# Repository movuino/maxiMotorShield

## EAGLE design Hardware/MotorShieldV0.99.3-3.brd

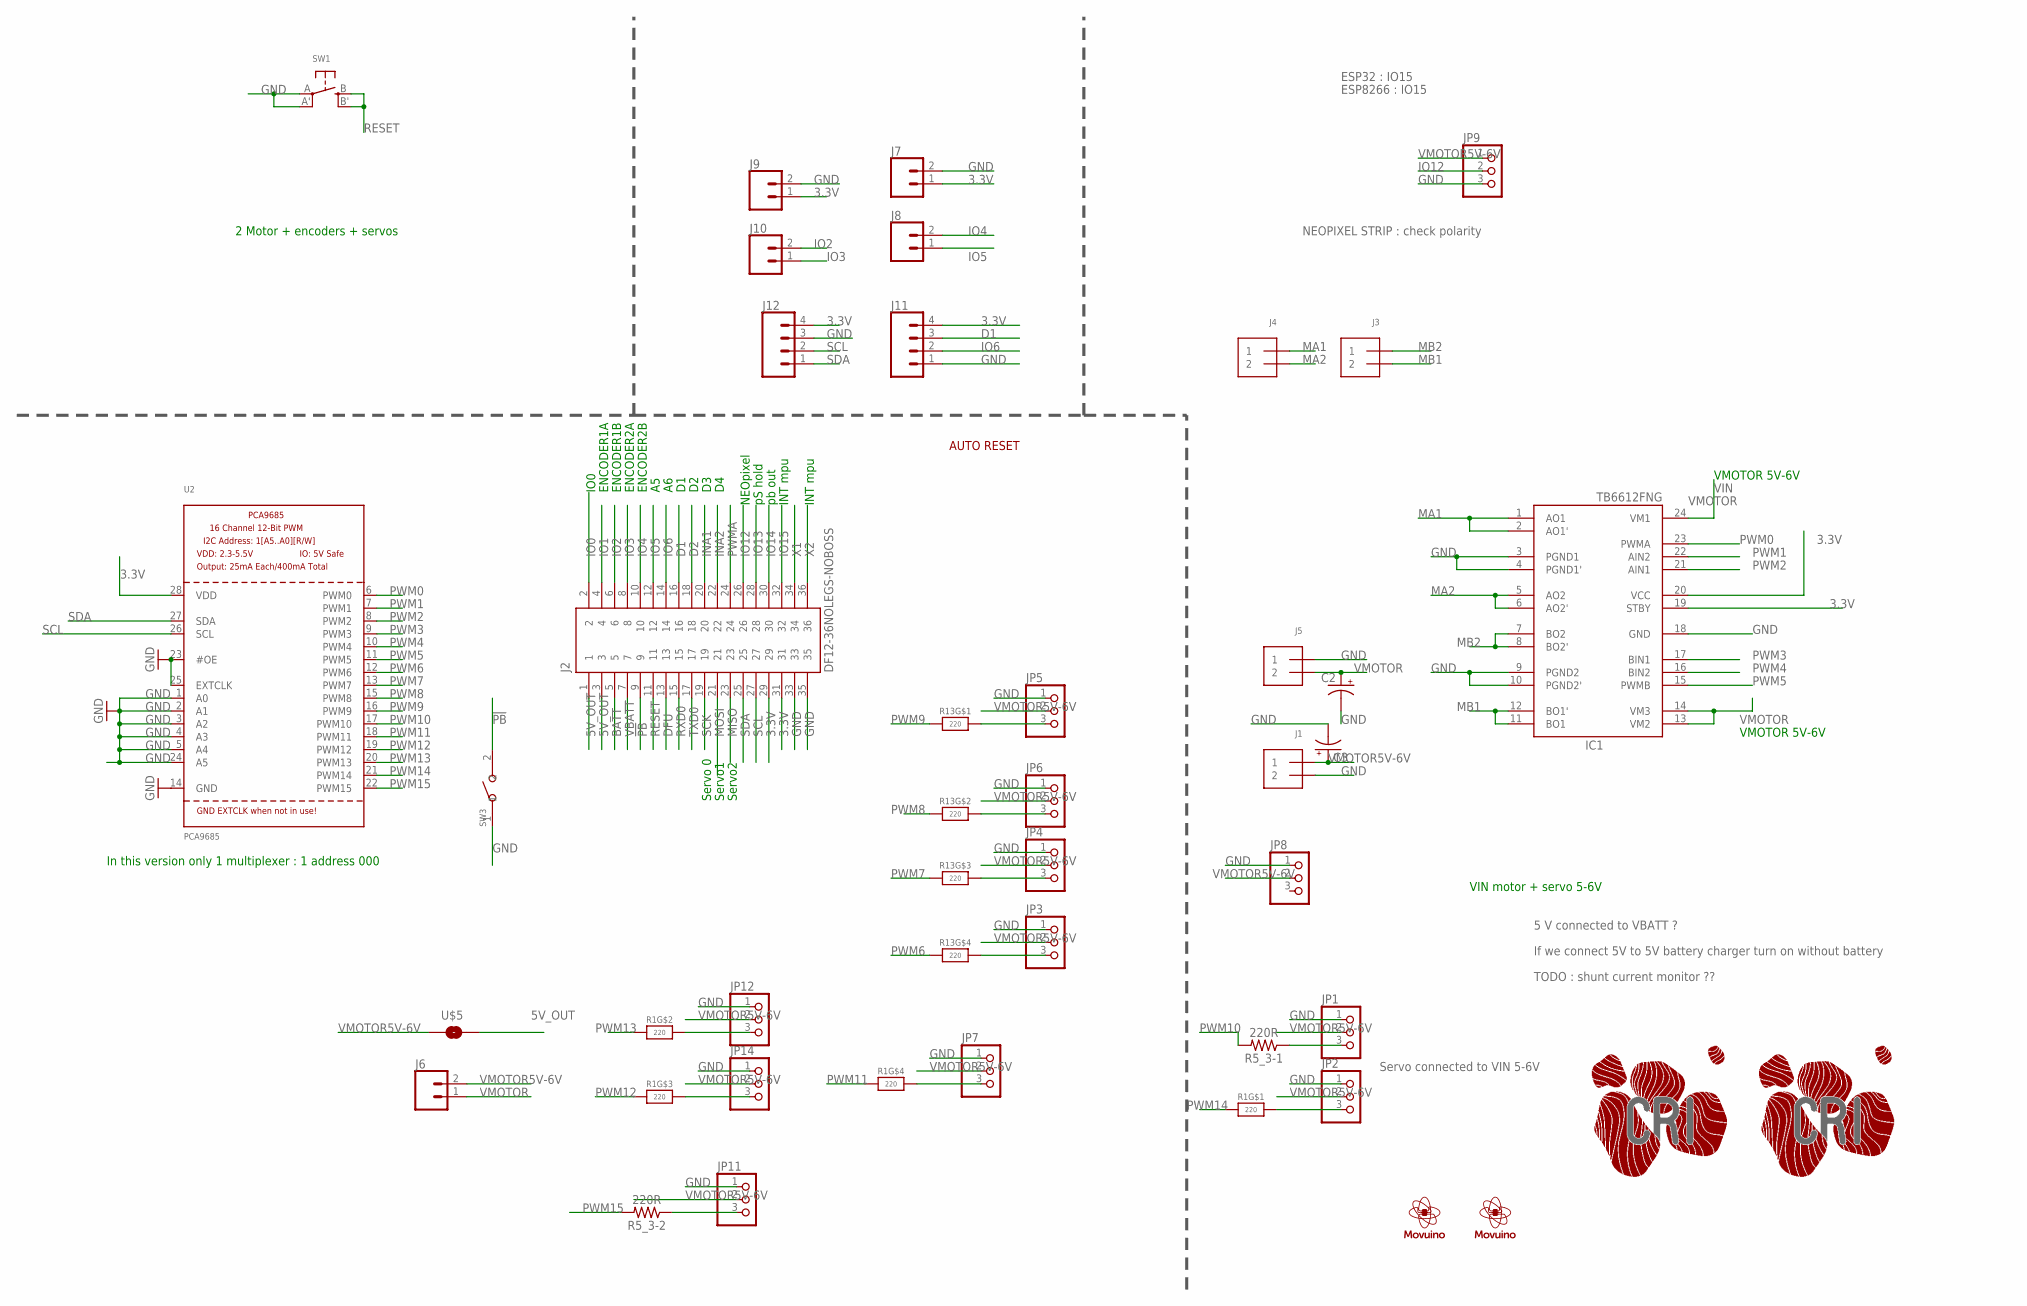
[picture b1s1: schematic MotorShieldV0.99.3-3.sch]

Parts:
C2, C3: CPOL-USE3.5-8; E3,5-8
IC1: TB6612FNG; SSOP24
J1, J3, J4, J5: TERMBLOCK_1X2; TERMBLOCK_1X2-3.5MM
J2: DF12-36NOLEGS-NOBOSS; DF12-36-DP-NL-NB
J6, J7, J8, J9, J10: CONN_02; 1X02
J11, J12: CONN_04; 1X04
JP1, JP2, JP3, JP4, JP5, JP6, JP7, JP8, JP9, JP11, JP12, JP14: PINHD-1X3; 1X03
R1, R13: 220; RESPACK_4X0603
R5_3-1, R5_3-2: 220R; R0402-SMALL-TDOCU
SW1: SWITCH_TACT_SMT; EVQ-Q2
SW3: DIP-BUTTON(2P-6.0X3.0X4.3MM)-TS-1101F; SW2-5.0-6.0X3.0X4.3MM
U2: PCA9685; TSSOP28
U$1: LOGO_MOVUINOTOP; LOGO_MOVUINO_BMP_10MM
U$2, U$3: LOGO-CRI-NEW-110MM-BOTTOM-SILK; LOGO_CRI-NEW-BMP10MM-BOTTOM
U$5: 0402-JUMPERCLOSED-DEFAULT; 0402-JUMPER-CLOSED
U$8: LOGO_MOVUINOBOTTOM_11MM; LOGO_MOVUINO_BMP_11MM-BOTTOM

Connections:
3.3V: IC1.19 (STBY), IC1.20 (VCC), J2.29, J2.31, J7.1, J9.1, J11.4, J12.4, U2.28 (VDD)
5V_OUT: J2.1, J2.3, U$5.2
!PB!: J2.9, SW3.2
BATT: J2.5
D1: J2.16, J11.3
D2: J2.18
DFU: J2.13
GND: C2.-, C3.-, IC1.3 (PGND1), IC1.4 (PGND1'), IC1.9 (PGND2), IC1.10 (PGND2'), IC1.18 (GND), J1.2, J2.33, J2.35, J5.1, J7.2, J9.2, J11.1, J12.3, JP1.1, JP2.1, JP3.1, JP4.1, JP5.1, JP6.1, JP7.1, JP8.1, JP9.3, JP11.1, JP12.1, JP14.1, SW1.A, SW1.A' (P1), SW3.1, U2.1 (A0), U2.2 (A1), U2.3 (A2), U2.4 (A3), U2.5 (A4), U2.14 (GND), U2.23 (#OE), U2.24 (A5), U2.25 (EXTCLK)
INA1: J2.20
INA2: J2.22
IO0: J2.2
IO1: J2.4
IO2: J2.6, J10.2
IO3: J2.8, J10.1
IO4: J2.10, J8.2
IO5: J2.12, J8.1
IO6: J2.14, J11.2
IO12: J2.26, JP9.2
IO13: J2.28
IO14: J2.30
IO15: J2.32
MA1: IC1.1 (AO1), IC1.2 (AO1'), J4.1
MA2: IC1.5 (AO2), IC1.6 (AO2'), J4.2
MB1: IC1.11 (BO1), IC1.12 (BO1'), J3.2
MB2: IC1.7 (BO2), IC1.8 (BO2'), J3.1
MISO: J2.23
MOSI: J2.21
unnamed: JP5.3, R13.8 (2)
unnamed: JP6.3, R13.7 (2)
unnamed: JP4.3, R13.6 (2)
unnamed: JP3.3, R13.5 (2)
unnamed: JP1.3, R5_3-1.1
unnamed: JP2.3, R1.8 (2)
unnamed: JP12.3, R1.7 (2)
unnamed: JP14.3, R1.6 (2)
unnamed: JP7.3, R1.5 (2)
unnamed: JP11.3, R5_3-2.1
PWM0: IC1.23 (PWMA), U2.6 (PWM0)
PWM1: IC1.22 (AIN2), U2.7 (PWM1)
PWM2: IC1.21 (AIN1), U2.8 (PWM2)
PWM3: IC1.17 (BIN1), U2.9 (PWM3)
PWM4: IC1.16 (BIN2), U2.10 (PWM4)
PWM5: IC1.15 (PWMB), U2.11 (PWM5)
PWM6: R13.4 (1), U2.12 (PWM6)
PWM7: R13.3 (1), U2.13 (PWM7)
PWM8: R13.2 (1), U2.15 (PWM8)
PWM9: R13.1, U2.16 (PWM9)
PWM10: R5_3-1.2, U2.17 (PWM10)
PWM11: R1.4 (1), U2.18 (PWM11)
PWM12: R1.3 (1), U2.19 (PWM12)
PWM13: R1.2 (1), U2.20 (PWM13)
PWM14: R1.1, U2.21 (PWM14)
PWM15: R5_3-2.2, U2.22 (PWM15)
PWMA: J2.24
RESET: J2.11, SW1.B (S), SW1.B' (S1)
RXD0: J2.15
SCK: J2.19
SCL: J2.27, J12.2, U2.26 (SCL)
SDA: J2.25, J12.1, U2.27 (SDA)
TXD0: J2.17
VBATT: J2.7
VMOTOR: C2.+, IC1.13 (VM2), IC1.14 (VM3), IC1.24 (VM1), J5.2, J6.1
VMOTOR5V-6V: C3.+, J1.1, J6.2, JP1.2, JP2.2, JP3.2, JP4.2, JP5.2, JP6.2, JP7.2, JP8.2, JP9.1, JP11.2, JP12.2, JP14.2, U$5.1
X1: J2.34
X2: J2.36

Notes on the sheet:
AUTO RESET
5 V connected to VBATT ?
If we connect 5V to 5V battery charger turn on without battery
VIN
VMOTOR 5V-6V
Servo connected to VIN 5-6V
TODO : shunt current monitor ??
ENCODER2B
ENCODER2A
ENCODER1B
ENCODER1A
IO0
NEOpixel
pS hold
pb out
INT mpu
Servo 0
Servo1
Servo2
In this version only 1 multiplexer : 1 address 000
2 Motor + encoders + servos
VIN motor + servo 5-6V
NEOPIXEL STRIP : check polarity
ESP8266 : IO15
ESP32 : IO15

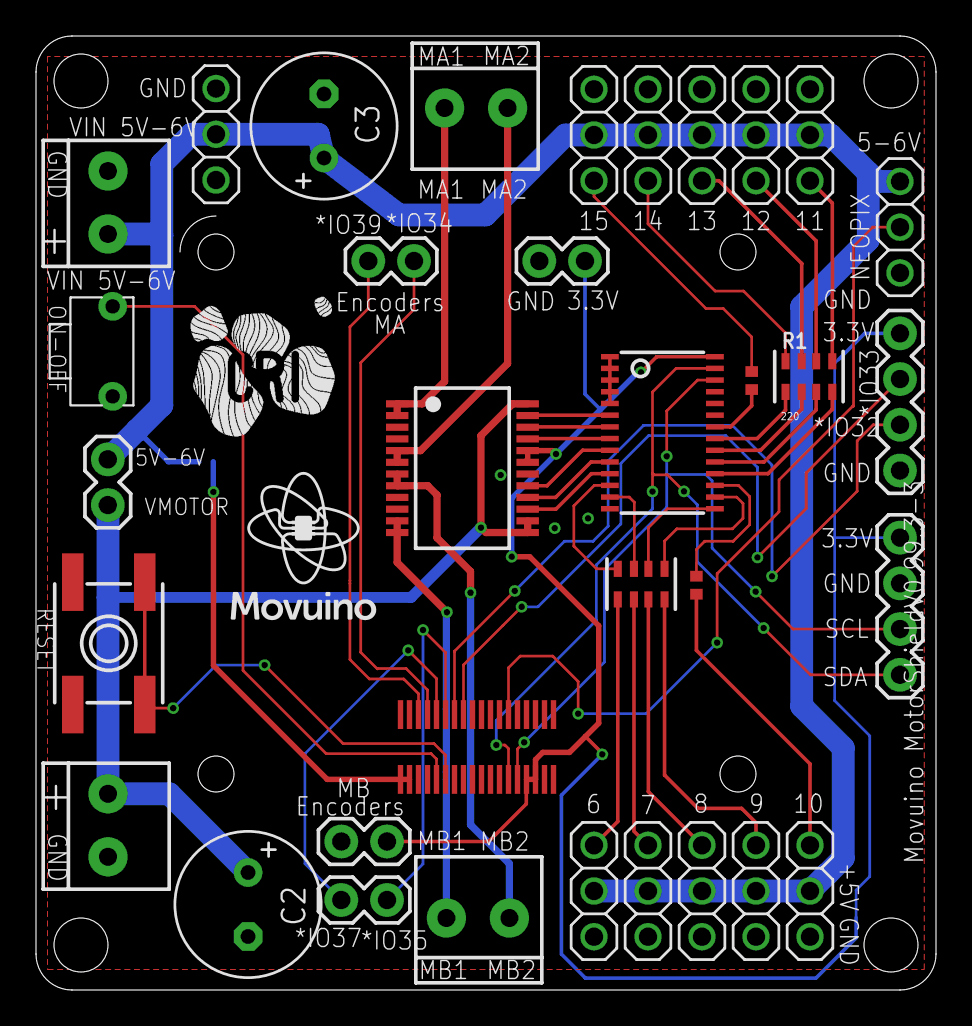
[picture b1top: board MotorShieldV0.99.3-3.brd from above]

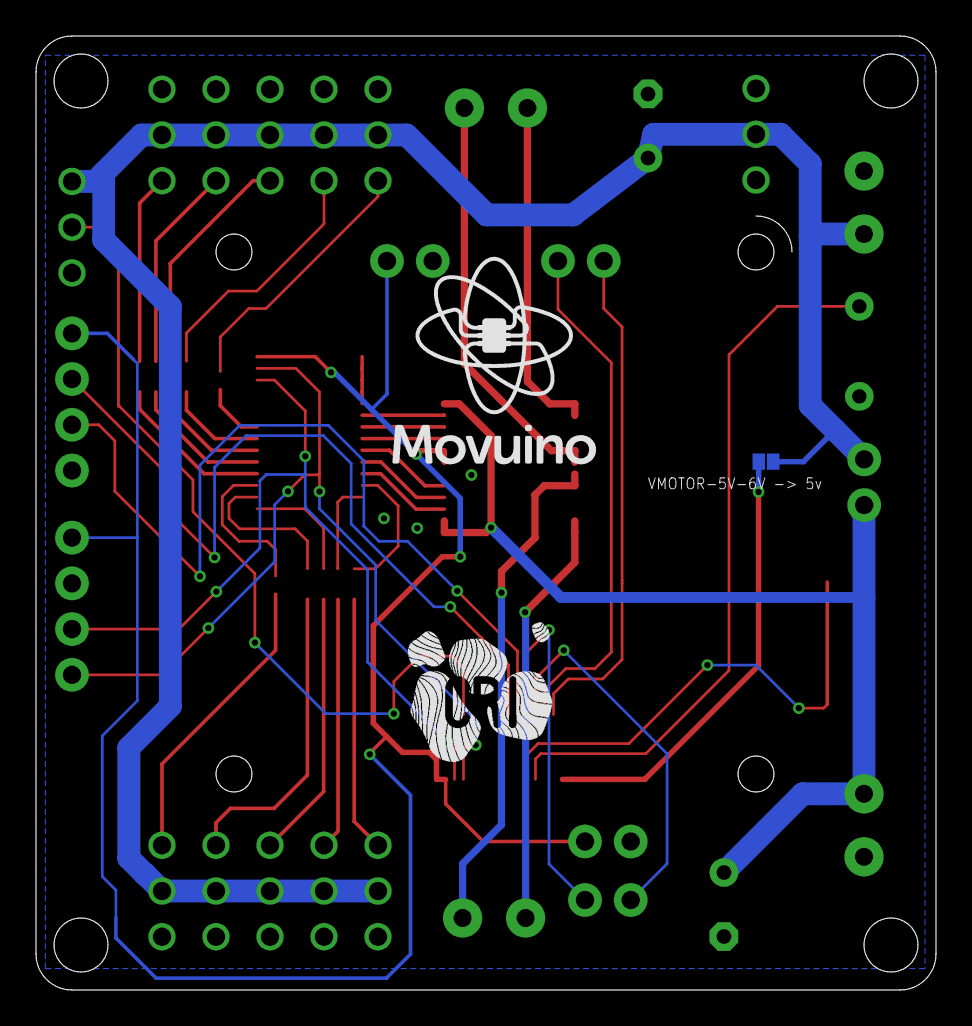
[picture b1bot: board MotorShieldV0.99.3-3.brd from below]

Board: 2 copper layers, 50.0 x 53.0 mm, 39 parts (2 on the bottom side), 46 nets.

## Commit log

2020-12-16 unitial commit

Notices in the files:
parts and their libraries:
microbuilder: This work is placed in the public domain, and may be freely used for commercial and non-commercial work with the following conditions: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
SparkFun-Connectors: Licensing: Creative Commons ShareAlike 4.0 International - https://creativecommons.org/licenses/by-sa/4.0
